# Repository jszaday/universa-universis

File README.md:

# Universa Universis
Retrofit PCB for various Alps full-sized keyboards.

## Planned support:
- AEK (ANSI, EUR, JPN)
- DELL AT101W (ANSI, EUR, JPN)
- DELL AT101 (ANSI, EUR, JPN)
- Strong Man SMK-8851 (BAE, JPN)

## Version History:

### Alpha Revision

Front:

Back:

#### Known Issues
- DELL AT101 support impeded by unpopable popout between RAlt and RCtrl.
- ISO Enter in wrong position (1.5u vs. 1u); can fold down leads of switch to compensate.
- Num pad plus and enter key switches rotated 180° (not a significant issue).
- No LED carrier board.

### Beta Revision (rev. 1/β, in progress)

Unbuilt and untested: nothing in this revision has been fabricated or run on a real board yet.

Design changes from the Alpha revision:
- Each keyboard piece except the F-nav piece has its own I2C GPIO extender (MCP23017) and a local key matrix, and the pieces connect through a four-wire I2C bus connector instead of hand-wired jumpers. The F-nav keys (PrtSc, ScrLk, Pause) reach the Nav piece's extender over a separate four-wire matrix cable (`docs/rev1-spec.md` D3).
- Diodes are on the back side of the board.
- The switches no longer carry the lock-LED defect.
- KiCad symbol and footprint library tables are project-local.
- On the rev1 PCB branch, the AT101 popout has a perforation ring.

Status of the Alpha known issues:

| Alpha issue | Rev. 1 status |
| --- | --- |
| AT101 popout cannot be popped out | Perforation ring added in the layout; untested on a real board |
| ISO Enter position | Not changed; under review |
| Numpad plus and Enter rotation | Not changed; see `TODO.md` |
| No LED carrier board | Four-pin header provided; carrier board not designed |

Open work is tracked in `TODO.md`; the electrical design is in `docs/rev1-spec.md`.

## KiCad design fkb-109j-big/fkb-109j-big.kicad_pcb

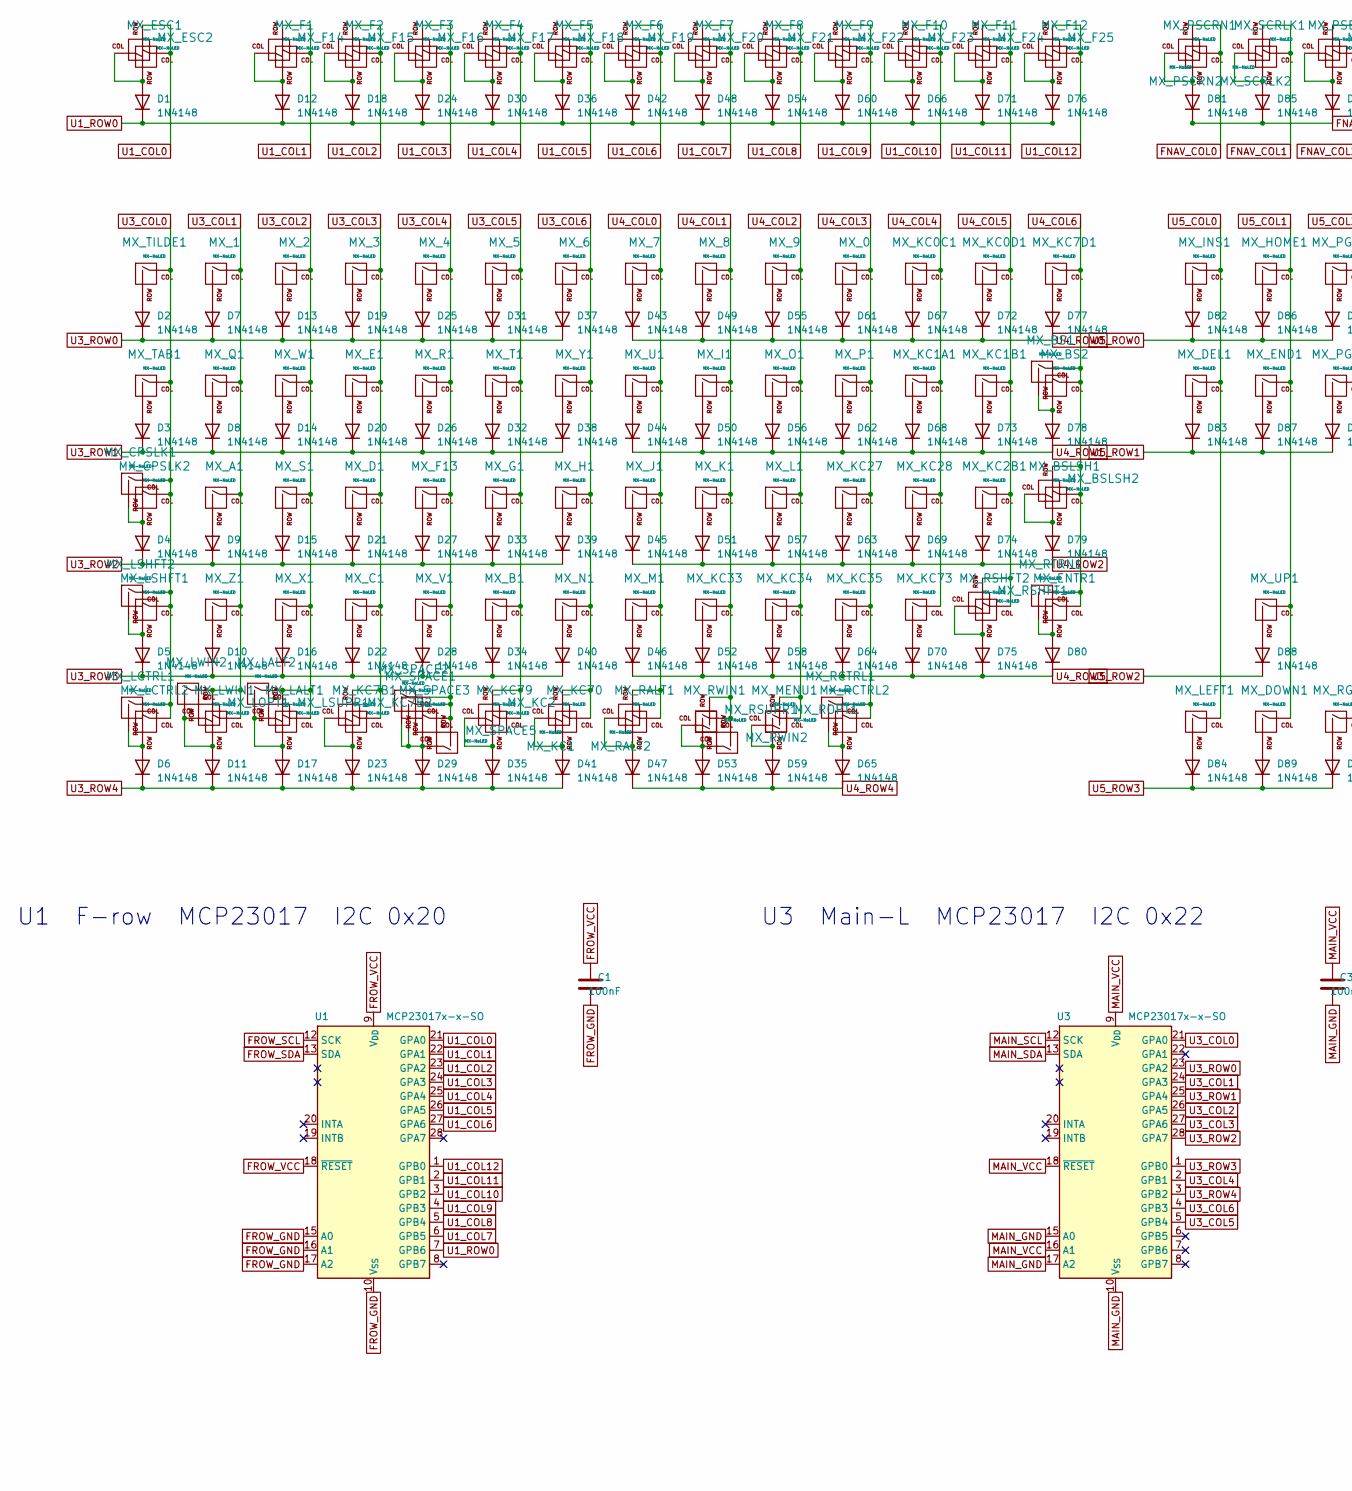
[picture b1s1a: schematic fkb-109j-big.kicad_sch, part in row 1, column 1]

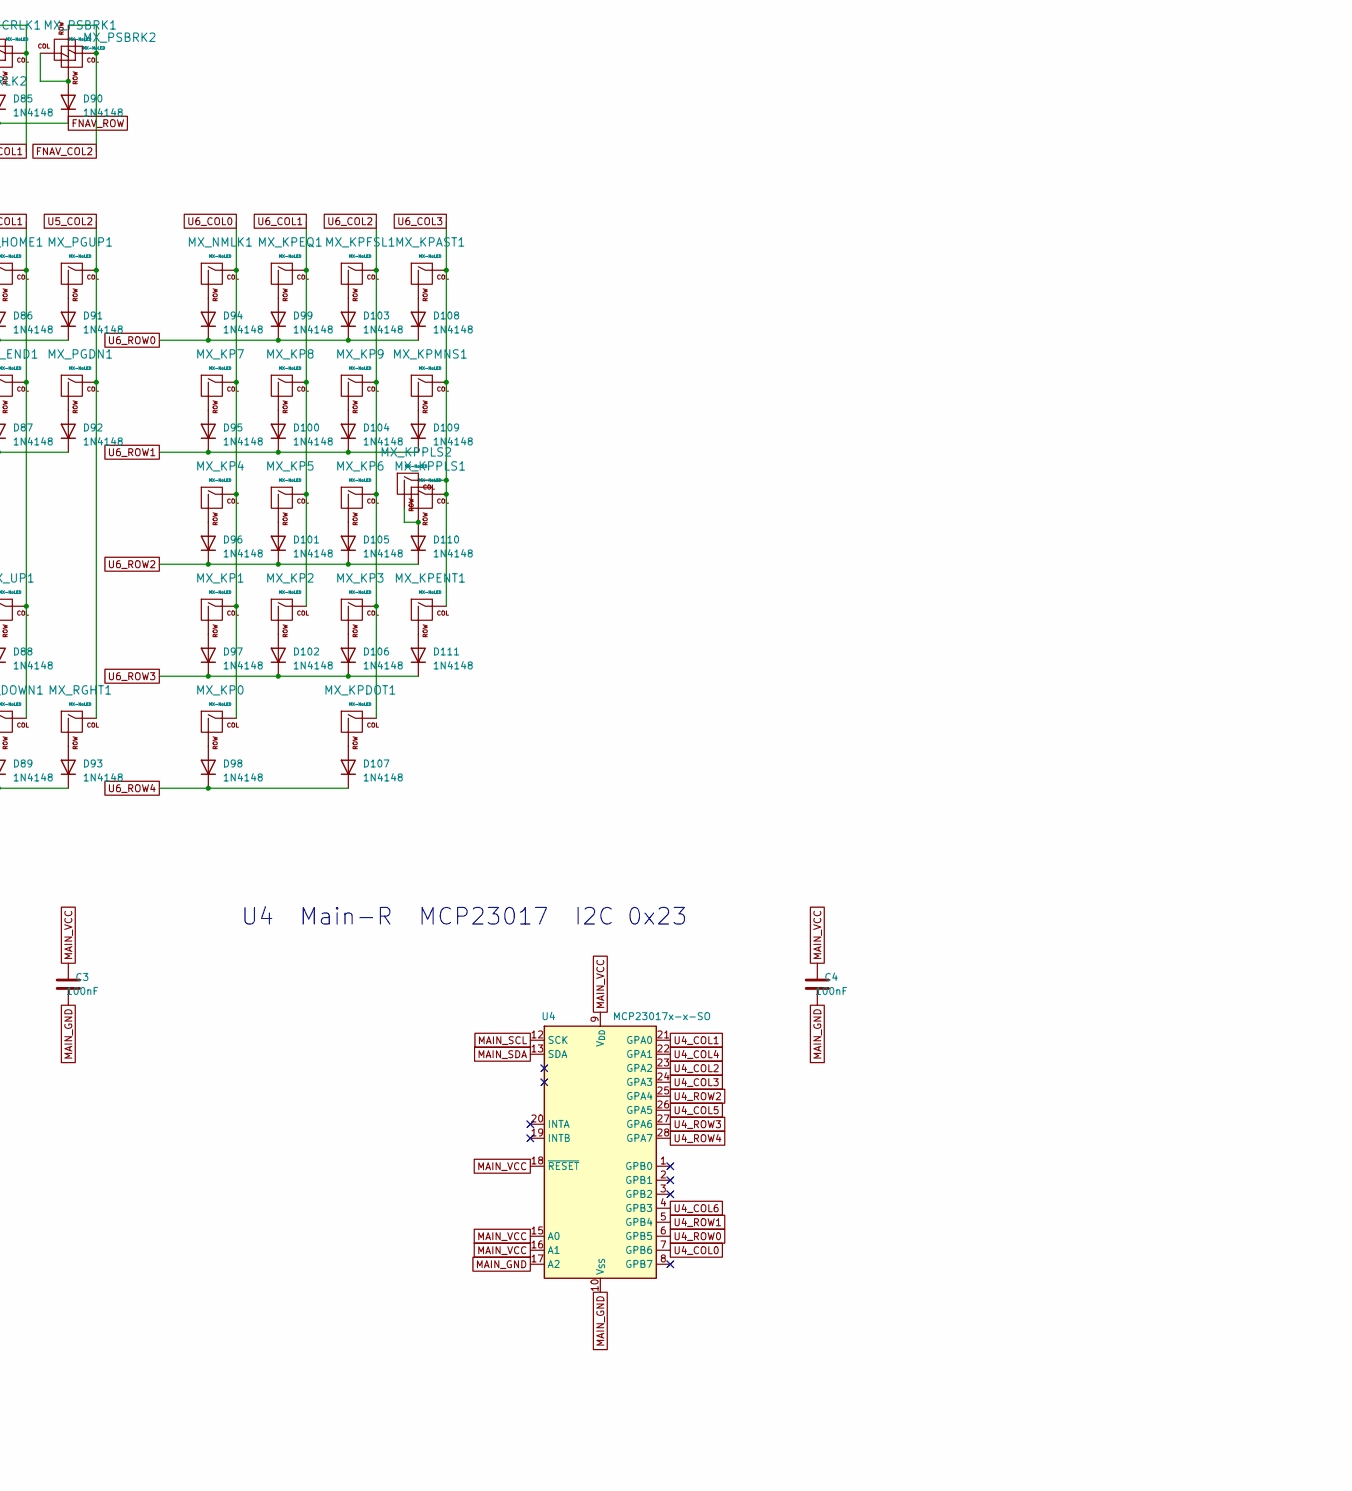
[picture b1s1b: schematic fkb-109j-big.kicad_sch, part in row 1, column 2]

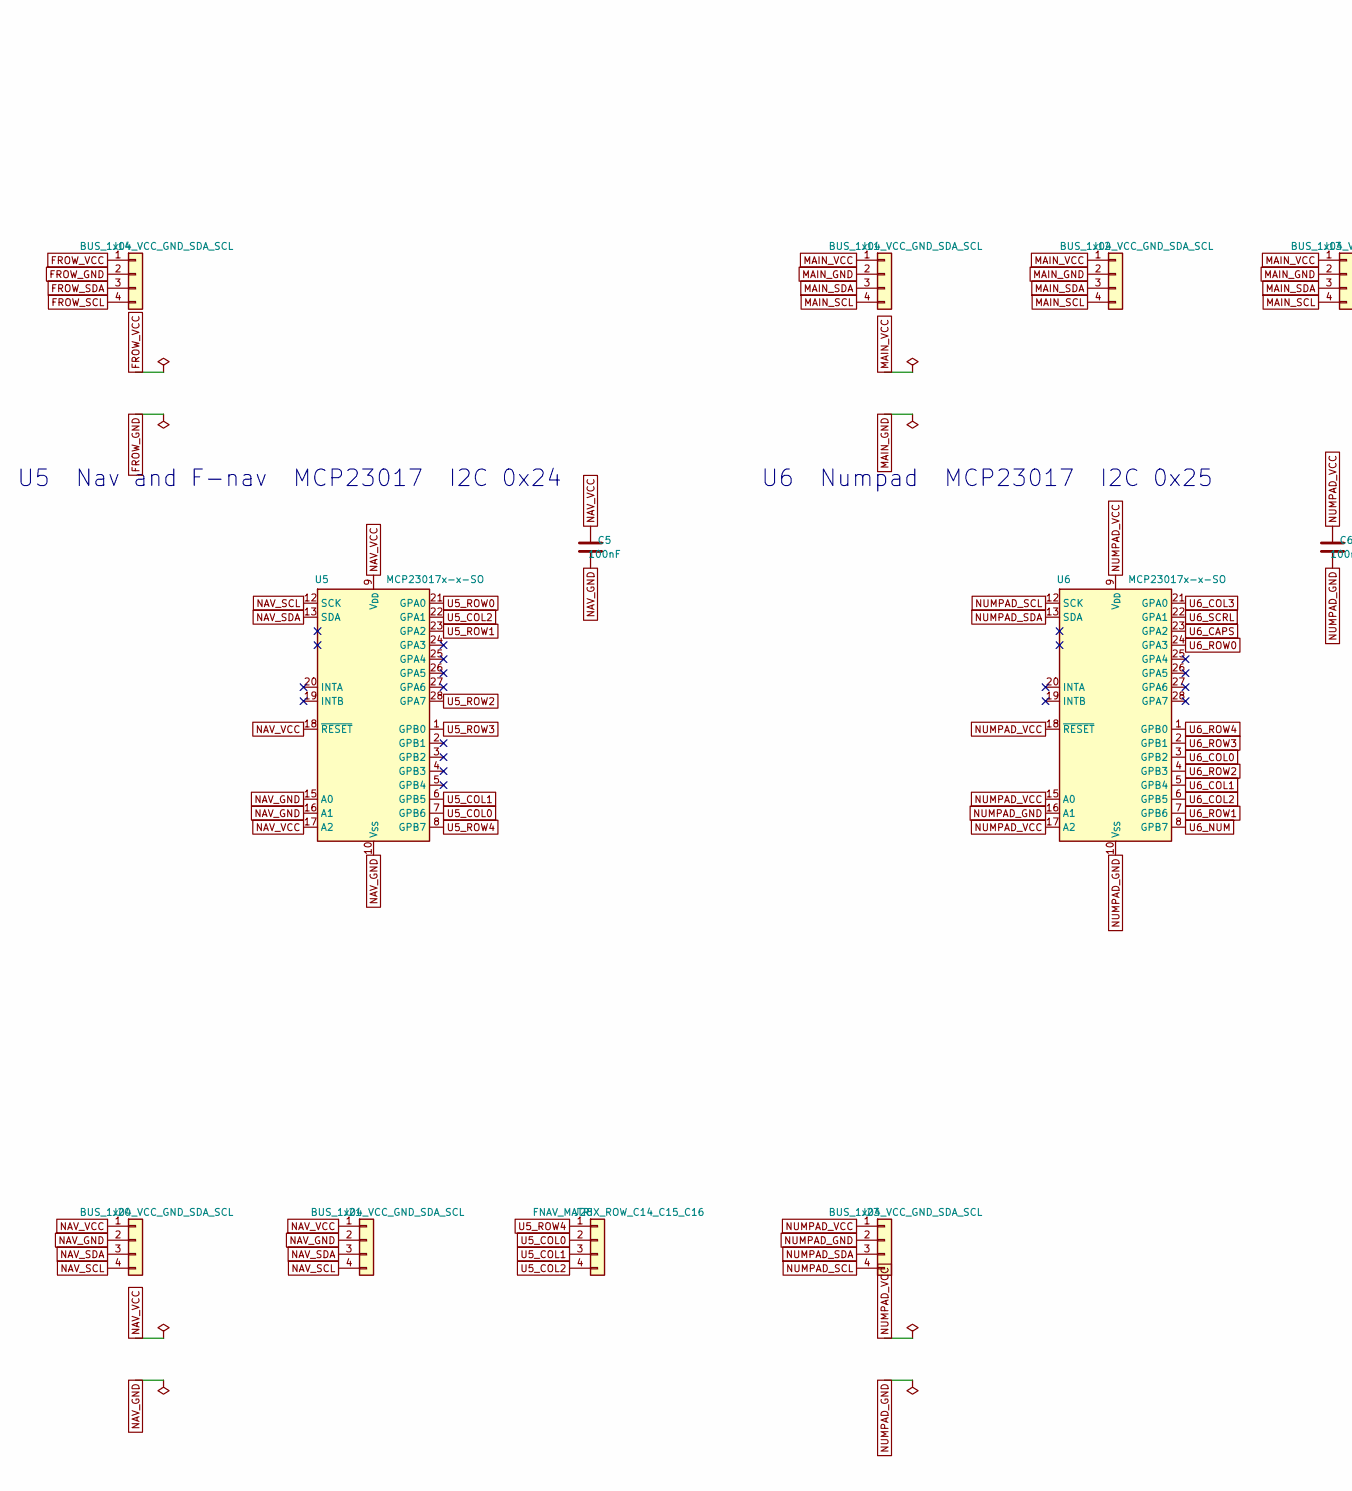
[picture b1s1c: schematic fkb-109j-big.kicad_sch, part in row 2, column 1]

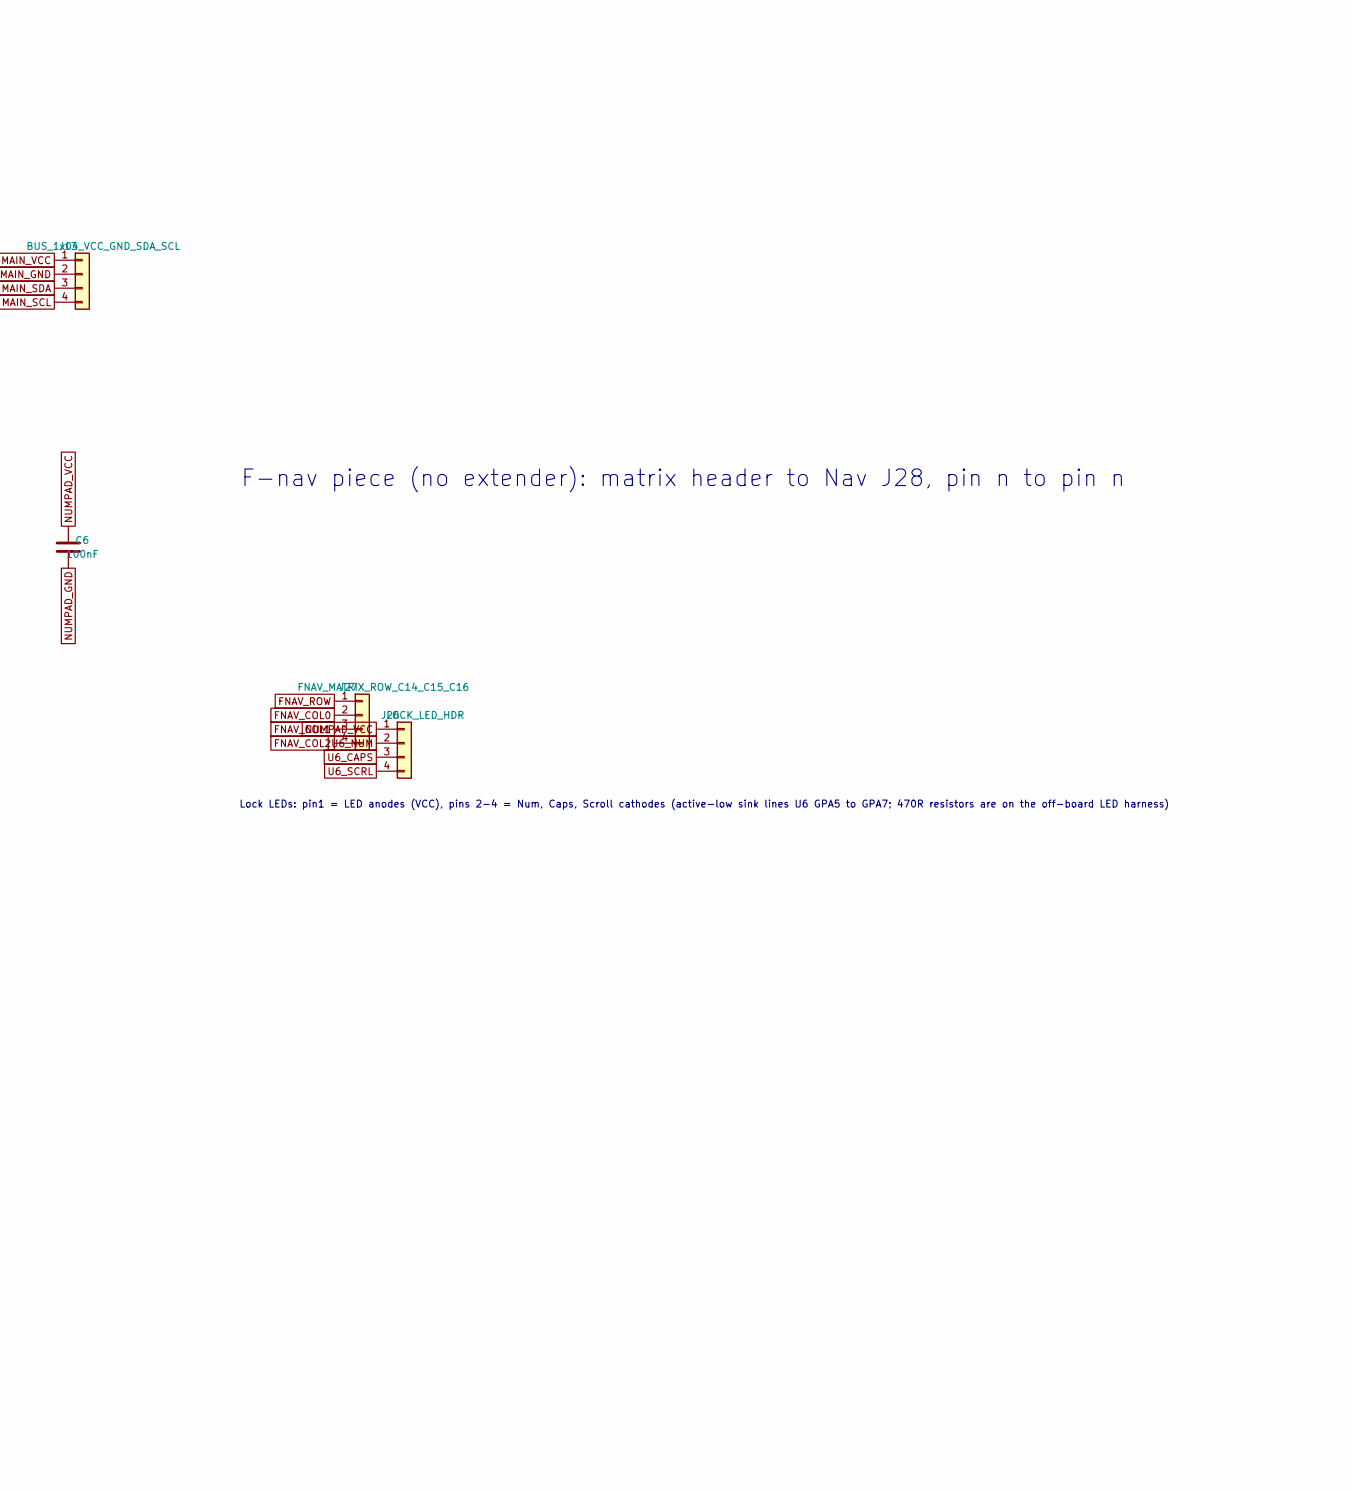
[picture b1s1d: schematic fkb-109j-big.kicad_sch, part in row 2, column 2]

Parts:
C1, C3, C4, C5, C6: 100nF; C_0805_2012Metric
D1, D2, D3, D4, D5, D6, D7, D8, D9, D10, D11, D12, D13, D14, D15, D16, D17, D18, D19, D20, D21, D22, D23, D24, D25, D26, D27, D28, D29, D30, D31, D32, D33, D34, D35, D36, D37, D38, D39, D40, D41, D42, D43, D44, D45, D46, D47, D48, D49, D50, D51, D52, D53, D54, D55, D56, D57, D58, D59, D60, D61, D62, D63, D64, D65, D66, D67, D68, D69, D70, D71, D72, D73, D74, D75, D76, D77, D78, D79, D80, D81, D82, D83, D84, D85, D86, D87, D88, D89, D90, D91, D92, D93, D94, D95, D96, D97, D98, D99, D100, D101, D102, D103, D104, D105, D106, D107, D108, D109, D110, D111: 1N4148; D_DO-35_P7.62mm_Horizontal_CathodeMark
J11, J12, J13, J14, J20, J21, J23: BUS_1x04_VCC_GND_SDA_SCL; PinHeader_1x04_P2.54mm_Vertical
J26: LOCK_LED_HDR; PinHeader_1x04_P2.54mm_Vertical
J27, J28: FNAV_MATRIX_ROW_C14_C15_C16; PinHeader_1x04_P2.54mm_Vertical
MX_0, MX_1, MX_2, MX_3, MX_4, MX_5, MX_6, MX_7, MX_8, MX_9: MX-NoLED; ALPS-1U
MX_A1: MX-NoLED; ALPS-1U
MX_B1: MX-NoLED; ALPS-1U
MX_BS1: MX-NoLED; ALPS-1U
MX_BS2: MX-NoLED; ALPS-2U
MX_BSLSH1: MX-NoLED; ALPS-1.5U
MX_BSLSH2: MX-NoLED; ALPS-1U
MX_C1: MX-NoLED; ALPS-1U
MX_CPSLK1: MX-NoLED; ALPS-1.5U
MX_CPSLK2: MX-NoLED; ALPS-1.75U
MX_D1: MX-NoLED; ALPS-1U
MX_DEL1: MX-NoLED; ALPS-1U
MX_DOWN1: MX-NoLED; ALPS-1U
MX_E1: MX-NoLED; ALPS-1U
MX_END1: MX-NoLED; ALPS-1U
MX_ENTR1: MX-NoLED; ALPS-2U
MX_ESC1, MX_ESC2: MX-NoLED; ALPS-1U
MX_F1, MX_F2, MX_F3, MX_F4, MX_F5, MX_F6, MX_F7, MX_F8, MX_F9, MX_F10, MX_F11, MX_F12, MX_F13, MX_F14, MX_F15, MX_F16, MX_F17, MX_F18, MX_F19, MX_F20, MX_F21, MX_F22, MX_F23, MX_F24, MX_F25: MX-NoLED; ALPS-1U
MX_G1: MX-NoLED; ALPS-1U
MX_H1: MX-NoLED; ALPS-1U
MX_HOME1: MX-NoLED; ALPS-1U
MX_I1: MX-NoLED; ALPS-1U
MX_INS1: MX-NoLED; ALPS-1U
MX_J1: MX-NoLED; ALPS-1U
MX_K1: MX-NoLED; ALPS-1U
MX_KC0C1, MX_KC0D1, MX_KC1A1, MX_KC1B1, MX_KC2B1, MX_KC7D1, MX_KC27, MX_KC28, MX_KC33, MX_KC34, MX_KC35, MX_KC73: MX-NoLED; ALPS-1U
MX_KC1: MX-NoLED; ALPS-1.5U
MX_KC2, MX_KC7B2: MX-NoLED; ALPS-1.75U
MX_KC7B1, MX_KC70, MX_KC79: MX-NoLED; ALPS-1.25U
MX_KP0: MX-NoLED; ALPS-2U
MX_KP1, MX_KP2, MX_KP3, MX_KP4, MX_KP5, MX_KP6, MX_KP7, MX_KP8, MX_KP9: MX-NoLED; ALPS-1U
MX_KPAST1: MX-NoLED; ALPS-1U
MX_KPDOT1: MX-NoLED; ALPS-1U
MX_KPENT1: MX-NoLED; ALPS-2U
MX_KPEQ1: MX-NoLED; ALPS-1U
MX_KPFSL1: MX-NoLED; ALPS-1U
MX_KPMNS1: MX-NoLED; ALPS-1U
MX_KPPLS1: MX-NoLED; ALPS-1U
MX_KPPLS2: MX-NoLED; ALPS-2U
MX_L1: MX-NoLED; ALPS-1U
MX_LALT1: MX-NoLED; ALPS-1.25U
MX_LALT2: MX-NoLED; ALPS-1.5U
MX_LCTRL1: MX-NoLED; ALPS-1.25U
MX_LCTRL2: MX-NoLED; ALPS-1.5U
MX_LEFT1: MX-NoLED; ALPS-1U
MX_LOPT1: MX-NoLED; ALPS-1.25U
MX_LSHFT1: MX-NoLED; ALPS-2.25U
MX_LSHFT2: MX-NoLED; ALPS-1.25U
MX_LSUPR1: MX-NoLED; ALPS-1.5U
MX_LWIN1: MX-NoLED; ALPS-1.25U
MX_LWIN2: MX-NoLED; ALPS-1U
MX_M1: MX-NoLED; ALPS-1U
MX_MENU1: MX-NoLED; ALPS-1.25U
MX_N1: MX-NoLED; ALPS-1U
MX_NMLK1: MX-NoLED; ALPS-1U
MX_O1: MX-NoLED; ALPS-1U
MX_P1: MX-NoLED; ALPS-1U
MX_PGDN1: MX-NoLED; ALPS-1U
MX_PGUP1: MX-NoLED; ALPS-1U
MX_PSBRK1, MX_PSBRK2: MX-NoLED; ALPS-1U
MX_PSCRN1, MX_PSCRN2: MX-NoLED; ALPS-1U
MX_Q1: MX-NoLED; ALPS-1U
MX_R1: MX-NoLED; ALPS-1U
MX_RALT1: MX-NoLED; ALPS-1.25U
MX_RALT2: MX-NoLED; ALPS-1.5U
MX_RCTRL1: MX-NoLED; ALPS-1.25U
MX_RCTRL2: MX-NoLED; ALPS-1.5U
MX_RGHT1: MX-NoLED; ALPS-1U
MX_ROPT1: MX-NoLED; ALPS-1.25U
MX_RSHFT1: MX-NoLED; ALPS-2.75U
MX_RSHFT2: MX-NoLED; ALPS-1.75U
MX_RSUPR1: MX-NoLED; ALPS-1.5U
MX_RTRN1: MX-NoLED; ALPS-2.25U
MX_RWIN1: MX-NoLED; ALPS-1.25U
MX_RWIN2: MX-NoLED; ALPS-1U
MX_S1: MX-NoLED; ALPS-1U
MX_SCRLK1, MX_SCRLK2: MX-NoLED; ALPS-1U
MX_SPACE1: MX-NoLED; ALPS-6.5U
MX_SPACE2: MX-NoLED; ALPS-6.25U
MX_SPACE3: MX-NoLED; ALPS-2.5U
MX_SPACE5: MX-NoLED; ALPS-2U
MX_T1: MX-NoLED; ALPS-1U
MX_TAB1: MX-NoLED; ALPS-1.5U
MX_TILDE1: MX-NoLED; ALPS-1U
MX_U1: MX-NoLED; ALPS-1U
MX_UP1: MX-NoLED; ALPS-1U
MX_V1: MX-NoLED; ALPS-1U
MX_W1: MX-NoLED; ALPS-1U
MX_X1: MX-NoLED; ALPS-1U
MX_Y1: MX-NoLED; ALPS-1U
MX_Z1: MX-NoLED; ALPS-1U
U1, U3, U4, U5, U6: MCP23017x-x-SO; SOIC-28W_7.5x17.9mm_P1.27mm

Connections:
FNAV_COL0: J27.2, MX_PSCRN1.1 (COL), MX_PSCRN2.2 (ROW)
FNAV_COL1: J27.3, MX_SCRLK1.1 (COL), MX_SCRLK2.2 (ROW)
FNAV_COL2: J27.4, MX_PSBRK1.1 (COL), MX_PSBRK2.2 (ROW)
FNAV_ROW: D81.1 (K), D85.1 (K), D90.1 (K), J27.1
FROW_GND: C1.2, J14.2, U1.10 (V_{SS}), U1.15 (A0), U1.16 (A1), U1.17 (A2)
FROW_SCL: J14.4, U1.12 (SCK)
FROW_SDA: J14.3, U1.13 (SDA)
FROW_VCC: C1.1, J14.1, U1.9 (V_{DD}), U1.18 (~RESET)
MAIN_GND: C3.2, C4.2, J11.2, J12.2, J13.2, U3.10 (V_{SS}), U3.15 (A0), U3.17 (A2), U4.10 (V_{SS}), U4.17 (A2)
MAIN_SCL: J11.4, J12.4, J13.4, U3.12 (SCK), U4.12 (SCK)
MAIN_SDA: J11.3, J12.3, J13.3, U3.13 (SDA), U4.13 (SDA)
MAIN_VCC: C3.1, C4.1, J11.1, J12.1, J13.1, U3.9 (V_{DD}), U3.16 (A1), U3.18 (~RESET), U4.9 (V_{DD}), U4.15 (A0), U4.16 (A1), U4.18 (~RESET)
NAV_GND: C5.2, J20.2, J21.2, U5.10 (V_{SS}), U5.15 (A0), U5.16 (A1)
NAV_SCL: J20.4, J21.4, U5.12 (SCK)
NAV_SDA: J20.3, J21.3, U5.13 (SDA)
NAV_VCC: C5.1, J20.1, J21.1, U5.9 (V_{DD}), U5.17 (A2), U5.18 (~RESET)
NUMPAD_GND: C6.2, J23.2, U6.10 (V_{SS}), U6.16 (A1)
NUMPAD_SCL: J23.4, U6.12 (SCK)
NUMPAD_SDA: J23.3, U6.13 (SDA)
NUMPAD_VCC: C6.1, J23.1, J26.1, U6.9 (V_{DD}), U6.15 (A0), U6.17 (A2), U6.18 (~RESET)
unnamed: D1.2 (A), MX_ESC1.2 (ROW), MX_ESC2.1 (COL)
unnamed: D2.2 (A), MX_TILDE1.2 (ROW)
unnamed: D3.2 (A), MX_TAB1.2 (ROW)
unnamed: D4.2 (A), MX_CPSLK1.2 (ROW), MX_CPSLK2.2 (ROW)
unnamed: D5.2 (A), MX_LSHFT1.2 (ROW), MX_LSHFT2.2 (ROW)
unnamed: D6.2 (A), MX_LCTRL1.2 (ROW), MX_LCTRL2.2 (ROW)
unnamed: D7.2 (A), MX_1.2 (ROW)
unnamed: D8.2 (A), MX_Q1.2 (ROW)
unnamed: D9.2 (A), MX_A1.2 (ROW)
unnamed: D10.2 (A), MX_Z1.2 (ROW)
unnamed: D11.2 (A), MX_LOPT1.1 (COL), MX_LWIN1.2 (ROW), MX_LWIN2.2 (ROW)
unnamed: D12.2 (A), MX_F1.2 (ROW), MX_F14.1 (COL)
unnamed: D13.2 (A), MX_2.2 (ROW)
unnamed: D14.2 (A), MX_W1.2 (ROW)
unnamed: D15.2 (A), MX_S1.2 (ROW)
unnamed: D16.2 (A), MX_X1.2 (ROW)
unnamed: D17.2 (A), MX_LALT1.2 (ROW), MX_LALT2.2 (ROW), MX_LSUPR1.1 (COL)
unnamed: D18.2 (A), MX_F2.2 (ROW), MX_F15.1 (COL)
unnamed: D19.2 (A), MX_3.2 (ROW)
unnamed: D20.2 (A), MX_E1.2 (ROW)
unnamed: D21.2 (A), MX_D1.2 (ROW)
unnamed: D22.2 (A), MX_C1.2 (ROW)
unnamed: D23.2 (A), MX_KC7B1.2 (ROW), MX_KC7B2.1 (COL)
unnamed: D24.2 (A), MX_F3.2 (ROW), MX_F16.1 (COL)
unnamed: D25.2 (A), MX_4.2 (ROW)
unnamed: D26.2 (A), MX_R1.2 (ROW)
unnamed: D27.2 (A), MX_F13.2 (ROW)
unnamed: D28.2 (A), MX_V1.2 (ROW)
unnamed: D29.2 (A), MX_SPACE1.2 (ROW), MX_SPACE2.2 (ROW), MX_SPACE3.2 (ROW), MX_SPACE5.1 (COL)
unnamed: D30.2 (A), MX_F4.2 (ROW), MX_F17.1 (COL)
unnamed: D31.2 (A), MX_5.2 (ROW)
unnamed: D32.2 (A), MX_T1.2 (ROW)
unnamed: D33.2 (A), MX_G1.2 (ROW)
unnamed: D34.2 (A), MX_B1.2 (ROW)
unnamed: D35.2 (A), MX_KC2.1 (COL), MX_KC79.2 (ROW)
unnamed: D36.2 (A), MX_F5.2 (ROW), MX_F18.1 (COL)
unnamed: D37.2 (A), MX_6.2 (ROW)
unnamed: D38.2 (A), MX_Y1.2 (ROW)
unnamed: D39.2 (A), MX_H1.2 (ROW)
unnamed: D40.2 (A), MX_N1.2 (ROW)
unnamed: D41.2 (A), MX_KC1.1 (COL), MX_KC70.2 (ROW)
unnamed: D42.2 (A), MX_F6.2 (ROW), MX_F19.1 (COL)
unnamed: D43.2 (A), MX_7.2 (ROW)
unnamed: D44.2 (A), MX_U1.2 (ROW)
unnamed: D45.2 (A), MX_J1.2 (ROW)
unnamed: D46.2 (A), MX_M1.2 (ROW)
unnamed: D47.2 (A), MX_RALT1.2 (ROW), MX_RALT2.1 (COL)
unnamed: D48.2 (A), MX_F7.2 (ROW), MX_F20.1 (COL)
unnamed: D49.2 (A), MX_8.2 (ROW)
unnamed: D50.2 (A), MX_I1.2 (ROW)
unnamed: D51.2 (A), MX_K1.2 (ROW)
unnamed: D52.2 (A), MX_KC33.2 (ROW)
unnamed: D53.2 (A), MX_RSUPR1.1 (COL), MX_RWIN1.2 (ROW), MX_RWIN2.1 (COL)
unnamed: D54.2 (A), MX_F8.2 (ROW), MX_F21.1 (COL)
unnamed: D55.2 (A), MX_9.2 (ROW)
unnamed: D56.2 (A), MX_O1.2 (ROW)
unnamed: D57.2 (A), MX_L1.2 (ROW)
unnamed: D58.2 (A), MX_KC34.2 (ROW)
unnamed: D59.2 (A), MX_MENU1.2 (ROW), MX_ROPT1.1 (COL)
unnamed: D60.2 (A), MX_F9.2 (ROW), MX_F22.1 (COL)
unnamed: D61.2 (A), MX_0.2 (ROW)
unnamed: D62.2 (A), MX_P1.2 (ROW)
unnamed: D63.2 (A), MX_KC27.2 (ROW)
unnamed: D64.2 (A), MX_KC35.2 (ROW)
unnamed: D65.2 (A), MX_RCTRL1.2 (ROW), MX_RCTRL2.2 (ROW)
unnamed: D66.2 (A), MX_F10.2 (ROW), MX_F23.1 (COL)
unnamed: D67.2 (A), MX_KC0C1.2 (ROW)
unnamed: D68.2 (A), MX_KC1A1.2 (ROW)
unnamed: D69.2 (A), MX_KC28.2 (ROW)
unnamed: D70.2 (A), MX_KC73.2 (ROW)
unnamed: D71.2 (A), MX_F11.2 (ROW), MX_F24.1 (COL)
unnamed: D72.2 (A), MX_KC0D1.2 (ROW)
unnamed: D73.2 (A), MX_KC1B1.2 (ROW)
unnamed: D74.2 (A), MX_KC2B1.2 (ROW)
unnamed: D75.2 (A), MX_RSHFT1.1 (COL), MX_RSHFT2.2 (ROW)
unnamed: D76.2 (A), MX_F12.2 (ROW), MX_F25.1 (COL)
unnamed: D77.2 (A), MX_KC7D1.2 (ROW)
unnamed: D78.2 (A), MX_BS1.2 (ROW), MX_BS2.2 (ROW)
unnamed: D79.2 (A), MX_BSLSH1.2 (ROW), MX_BSLSH2.1 (COL)
unnamed: D80.2 (A), MX_ENTR1.2 (ROW), MX_RTRN1.2 (ROW)
unnamed: D81.2 (A), MX_PSCRN1.2 (ROW), MX_PSCRN2.1 (COL)
unnamed: D82.2 (A), MX_INS1.2 (ROW)
unnamed: D83.2 (A), MX_DEL1.2 (ROW)
unnamed: D84.2 (A), MX_LEFT1.2 (ROW)
unnamed: D85.2 (A), MX_SCRLK1.2 (ROW), MX_SCRLK2.1 (COL)
unnamed: D86.2 (A), MX_HOME1.2 (ROW)
unnamed: D87.2 (A), MX_END1.2 (ROW)
unnamed: D88.2 (A), MX_UP1.2 (ROW)
unnamed: D89.2 (A), MX_DOWN1.2 (ROW)
unnamed: D90.2 (A), MX_PSBRK1.2 (ROW), MX_PSBRK2.1 (COL)
unnamed: D91.2 (A), MX_PGUP1.2 (ROW)
unnamed: D92.2 (A), MX_PGDN1.2 (ROW)
unnamed: D93.2 (A), MX_RGHT1.2 (ROW)
unnamed: D94.2 (A), MX_NMLK1.2 (ROW)
unnamed: D95.2 (A), MX_KP7.2 (ROW)
unnamed: D96.2 (A), MX_KP4.2 (ROW)
unnamed: D97.2 (A), MX_KP1.2 (ROW)
unnamed: D98.2 (A), MX_KP0.2 (ROW)
unnamed: D99.2 (A), MX_KPEQ1.2 (ROW)
unnamed: D100.2 (A), MX_KP8.2 (ROW)
unnamed: D101.2 (A), MX_KP5.2 (ROW)
unnamed: D102.2 (A), MX_KP2.2 (ROW)
unnamed: D103.2 (A), MX_KPFSL1.2 (ROW)
unnamed: D104.2 (A), MX_KP9.2 (ROW)
unnamed: D105.2 (A), MX_KP6.2 (ROW)
unnamed: D106.2 (A), MX_KP3.2 (ROW)
unnamed: D107.2 (A), MX_KPDOT1.2 (ROW)
unnamed: D108.2 (A), MX_KPAST1.2 (ROW)
unnamed: D109.2 (A), MX_KPMNS1.2 (ROW)
unnamed: D110.2 (A), MX_KPPLS1.2 (ROW), MX_KPPLS2.2 (ROW)
unnamed: D111.2 (A), MX_KPENT1.2 (ROW)
U1_COL0: MX_ESC1.1 (COL), MX_ESC2.2 (ROW), U1.21 (GPA0)
U1_COL1: MX_F1.1 (COL), MX_F14.2 (ROW), U1.22 (GPA1)
U1_COL2: MX_F2.1 (COL), MX_F15.2 (ROW), U1.23 (GPA2)
U1_COL3: MX_F3.1 (COL), MX_F16.2 (ROW), U1.24 (GPA3)
U1_COL4: MX_F4.1 (COL), MX_F17.2 (ROW), U1.25 (GPA4)
U1_COL5: MX_F5.1 (COL), MX_F18.2 (ROW), U1.26 (GPA5)
U1_COL6: MX_F6.1 (COL), MX_F19.2 (ROW), U1.27 (GPA6)
U1_COL7: MX_F7.1 (COL), MX_F20.2 (ROW), U1.6 (GPB5)
U1_COL8: MX_F8.1 (COL), MX_F21.2 (ROW), U1.5 (GPB4)
U1_COL9: MX_F9.1 (COL), MX_F22.2 (ROW), U1.4 (GPB3)
U1_COL10: MX_F10.1 (COL), MX_F23.2 (ROW), U1.3 (GPB2)
U1_COL11: MX_F11.1 (COL), MX_F24.2 (ROW), U1.2 (GPB1)
U1_COL12: MX_F12.1 (COL), MX_F25.2 (ROW), U1.1 (GPB0)
U1_ROW0: D1.1 (K), D12.1 (K), D18.1 (K), D24.1 (K), D30.1 (K), D36.1 (K), D42.1 (K), D48.1 (K), D54.1 (K), D60.1 (K), D66.1 (K), D71.1 (K), D76.1 (K), U1.7 (GPB6)
U3_COL0: MX_CPSLK1.1 (COL), MX_CPSLK2.1 (COL), MX_LCTRL1.1 (COL), MX_LCTRL2.1 (COL), MX_LSHFT1.1 (COL), MX_LSHFT2.1 (COL), MX_TAB1.1 (COL), MX_TILDE1.1 (COL), U3.21 (GPA0)
U3_COL1: MX_1.1 (COL), MX_A1.1 (COL), MX_LOPT1.2 (ROW), MX_LWIN1.1 (COL), MX_LWIN2.1 (COL), MX_Q1.1 (COL), MX_Z1.1 (COL), U3.24 (GPA3)
U3_COL2: MX_2.1 (COL), MX_LALT1.1 (COL), MX_LALT2.1 (COL), MX_LSUPR1.2 (ROW), MX_S1.1 (COL), MX_W1.1 (COL), MX_X1.1 (COL), U3.26 (GPA5)
U3_COL3: MX_3.1 (COL), MX_C1.1 (COL), MX_D1.1 (COL), MX_E1.1 (COL), MX_KC7B1.1 (COL), MX_KC7B2.2 (ROW), U3.27 (GPA6)
U3_COL4: MX_4.1 (COL), MX_F13.1 (COL), MX_R1.1 (COL), MX_SPACE1.1 (COL), MX_SPACE2.1 (COL), MX_SPACE3.1 (COL), MX_SPACE5.2 (ROW), MX_V1.1 (COL), U3.2 (GPB1)
U3_COL5: MX_5.1 (COL), MX_B1.1 (COL), MX_G1.1 (COL), MX_KC2.2 (ROW), MX_KC79.1 (COL), MX_T1.1 (COL), U3.5 (GPB4)
U3_COL6: MX_6.1 (COL), MX_H1.1 (COL), MX_KC1.2 (ROW), MX_KC70.1 (COL), MX_N1.1 (COL), MX_Y1.1 (COL), U3.4 (GPB3)
U3_ROW0: D2.1 (K), D7.1 (K), D13.1 (K), D19.1 (K), D25.1 (K), D31.1 (K), D37.1 (K), U3.23 (GPA2)
U3_ROW1: D3.1 (K), D8.1 (K), D14.1 (K), D20.1 (K), D26.1 (K), D32.1 (K), D38.1 (K), U3.25 (GPA4)
U3_ROW2: D4.1 (K), D9.1 (K), D15.1 (K), D21.1 (K), D27.1 (K), D33.1 (K), D39.1 (K), U3.28 (GPA7)
U3_ROW3: D5.1 (K), D10.1 (K), D16.1 (K), D22.1 (K), D28.1 (K), D34.1 (K), D40.1 (K), U3.1 (GPB0)
U3_ROW4: D6.1 (K), D11.1 (K), D17.1 (K), D23.1 (K), D29.1 (K), D35.1 (K), D41.1 (K), U3.3 (GPB2)
U4_COL0: MX_7.1 (COL), MX_J1.1 (COL), MX_M1.1 (COL), MX_RALT1.1 (COL), MX_RALT2.2 (ROW), MX_U1.1 (COL), U4.7 (GPB6)
U4_COL1: MX_8.1 (COL), MX_I1.1 (COL), MX_K1.1 (COL), MX_KC33.1 (COL), MX_RSUPR1.2 (ROW), MX_RWIN1.1 (COL), MX_RWIN2.2 (ROW), U4.21 (GPA0)
U4_COL2: MX_9.1 (COL), MX_KC34.1 (COL), MX_L1.1 (COL), MX_MENU1.1 (COL), MX_O1.1 (COL), MX_ROPT1.2 (ROW), U4.23 (GPA2)
U4_COL3: MX_0.1 (COL), MX_KC27.1 (COL), MX_KC35.1 (COL), MX_P1.1 (COL), MX_RCTRL1.1 (COL), MX_RCTRL2.1 (COL), U4.24 (GPA3)
U4_COL4: MX_KC0C1.1 (COL), MX_KC1A1.1 (COL), MX_KC28.1 (COL), MX_KC73.1 (COL), U4.22 (GPA1)
U4_COL5: MX_KC0D1.1 (COL), MX_KC1B1.1 (COL), MX_KC2B1.1 (COL), MX_RSHFT1.2 (ROW), MX_RSHFT2.1 (COL), U4.26 (GPA5)
U4_COL6: MX_BS1.1 (COL), MX_BS2.1 (COL), MX_BSLSH1.1 (COL), MX_BSLSH2.2 (ROW), MX_ENTR1.1 (COL), MX_KC7D1.1 (COL), MX_RTRN1.1 (COL), U4.4 (GPB3)
U4_ROW0: D43.1 (K), D49.1 (K), D55.1 (K), D61.1 (K), D67.1 (K), D72.1 (K), D77.1 (K), U4.6 (GPB5)
U4_ROW1: D44.1 (K), D50.1 (K), D56.1 (K), D62.1 (K), D68.1 (K), D73.1 (K), D78.1 (K), U4.5 (GPB4)
U4_ROW2: D45.1 (K), D51.1 (K), D57.1 (K), D63.1 (K), D69.1 (K), D74.1 (K), D79.1 (K), U4.25 (GPA4)
U4_ROW3: D46.1 (K), D52.1 (K), D58.1 (K), D64.1 (K), D70.1 (K), D75.1 (K), D80.1 (K), U4.27 (GPA6)
U4_ROW4: D47.1 (K), D53.1 (K), D59.1 (K), D65.1 (K), U4.28 (GPA7)
U5_COL0: J28.2, MX_DEL1.1 (COL), MX_INS1.1 (COL), MX_LEFT1.1 (COL), U5.7 (GPB6)
U5_COL1: J28.3, MX_DOWN1.1 (COL), MX_END1.1 (COL), MX_HOME1.1 (COL), MX_UP1.1 (COL), U5.6 (GPB5)
U5_COL2: J28.4, MX_PGDN1.1 (COL), MX_PGUP1.1 (COL), MX_RGHT1.1 (COL), U5.22 (GPA1)
U5_ROW0: D82.1 (K), D86.1 (K), D91.1 (K), U5.21 (GPA0)
U5_ROW1: D83.1 (K), D87.1 (K), D92.1 (K), U5.23 (GPA2)
U5_ROW2: D88.1 (K), U5.28 (GPA7)
U5_ROW3: D84.1 (K), D89.1 (K), D93.1 (K), U5.1 (GPB0)
U5_ROW4: J28.1, U5.8 (GPB7)
U6_CAPS: J26.3, U6.23 (GPA2)
U6_COL0: MX_KP0.1 (COL), MX_KP1.1 (COL), MX_KP4.1 (COL), MX_KP7.1 (COL), MX_NMLK1.1 (COL), U6.3 (GPB2)
U6_COL1: MX_KP2.1 (COL), MX_KP5.1 (COL), MX_KP8.1 (COL), MX_KPEQ1.1 (COL), U6.5 (GPB4)
U6_COL2: MX_KP3.1 (COL), MX_KP6.1 (COL), MX_KP9.1 (COL), MX_KPDOT1.1 (COL), MX_KPFSL1.1 (COL), U6.6 (GPB5)
U6_COL3: MX_KPAST1.1 (COL), MX_KPENT1.1 (COL), MX_KPMNS1.1 (COL), MX_KPPLS1.1 (COL), MX_KPPLS2.1 (COL), U6.21 (GPA0)
U6_NUM: J26.2, U6.8 (GPB7)
U6_ROW0: D94.1 (K), D99.1 (K), D103.1 (K), D108.1 (K), U6.24 (GPA3)
U6_ROW1: D95.1 (K), D100.1 (K), D104.1 (K), D109.1 (K), U6.7 (GPB6)
U6_ROW2: D96.1 (K), D101.1 (K), D105.1 (K), D110.1 (K), U6.4 (GPB3)
U6_ROW3: D97.1 (K), D102.1 (K), D106.1 (K), D111.1 (K), U6.2 (GPB1)
U6_ROW4: D98.1 (K), D107.1 (K), U6.1 (GPB0)
U6_SCRL: J26.4, U6.22 (GPA1)

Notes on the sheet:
U1 F-row MCP23017 I2C 0x20
U3 Main-L MCP23017 I2C 0x22
U4 Main-R MCP23017 I2C 0x23
U5 Nav and F-nav MCP23017 I2C 0x24
U6 Numpad MCP23017 I2C 0x25
Lock LEDs: pin1 = LED anodes (VCC), pins 2-4 = Num, Caps, Scroll cathodes (active-low sink lines U6 GPA5 to GPA7; 470R resistors are on the off-board LED harness)
F-nav piece (no extender): matrix header to Nav J28, pin n to pin n

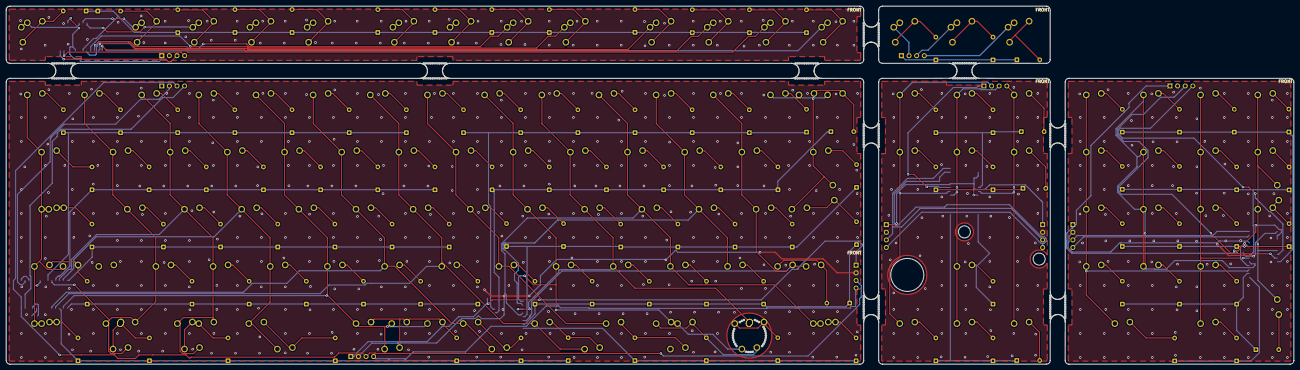
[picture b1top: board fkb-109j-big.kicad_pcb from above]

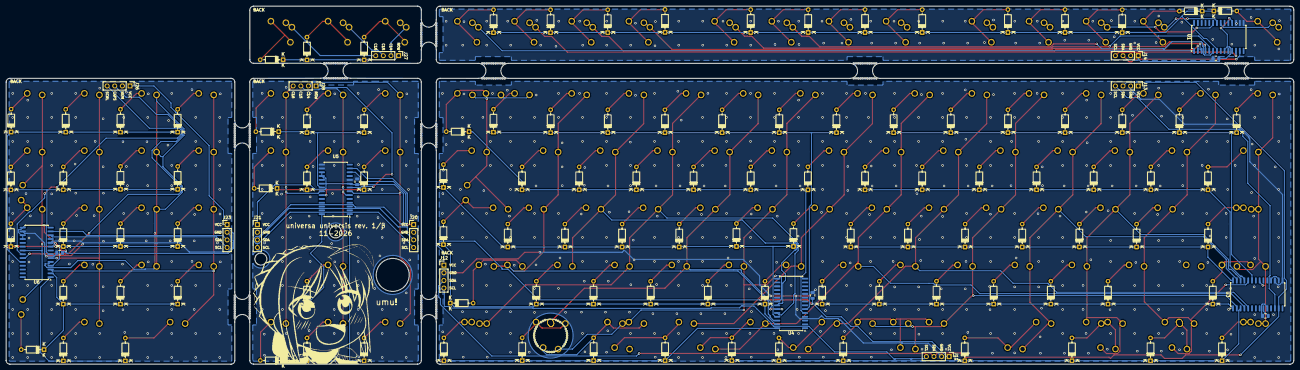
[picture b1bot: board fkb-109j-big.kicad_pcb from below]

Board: 2 copper layers, 429.1 x 119.3 mm, 291 parts (131 on the bottom side), 189 nets.

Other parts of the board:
MB1, MB2, MB3, MB4, MB5, MB6, MB7, MB8, MB9: VAL**; umu_mouse-bite-5mm-slot
RING1: POPOUT; umu_popout-ring-AT101
